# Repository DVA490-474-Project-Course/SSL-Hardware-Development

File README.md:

# SSL-Hardware-Development

## Overview
Welcome to the SSL Robot Project repository! This project encompasses both hardware and software components essential for building and controlling an SSL robot. Our goal is to create a robust, scalable, and maintainable robot platform.

## Repository Structure
- **3D_Models**: Contains all 3D models related to the robot design.
- **Circuits**: Circuit designs for various robot components.
- **BOM**: Bill of Materials for each component.
- **Software**: Firmware and software for motor control and other functionalities.
- **Design_Documents**: Technical specifications and design decisions.
- **Meeting_Notes**: Documentation of project meetings.
- **Misc**: Miscellaneous files and references.
- **Simulations**: Simulation scripts and models.
- **Documentation**: Comprehensive project documentation and guides.

```bash
/SSL-Robot-Project
├── /3D_Models
│   ├── /CAD_Files            # All CAD files for different robot parts
│   ├── /STL_Files            # STL exports for 3D printing
│   └── /Renderings           # Renders of the 3D models
├── /Circuits
│   ├── /Motor_Control        # Motor circuit design files
│   ├── /Kicker               # Kicker circuit design files
│   ├── /Dribbler             # Dribbler circuit design files
│   └── /Sensor               # Sensor circuit design files
├── /BOM                      # Bill of Materials for different components
├── /Software
│   ├── /Motor_Control
│   │   ├── /Firmware          # Firmware code for motor controllers
│   │   │   ├── /src           # Source code files
│   │   │   ├── /include       # Header files
│   │   │   ├── /tests         # Unit and integration tests
│   │   │   └── README.md      # Firmware-specific documentation
│   │   ├── /Software_Doc      # Documentation related to motor control software
│   │   │   ├── /API_Docs      # API documentation if applicable
│   │   │   └── /User_Guides   # User manuals or setup guides
│   │   ├── /Libraries         # Any libraries or dependencies specific to motor control
│   │   └── /Examples          # Example projects or usage scenarios
│   ├── /Kicker_Control        # Similar structure for kicker control software
│   ├── /Dribbler_Control      # Similar structure for dribbler control software
│   └── /Sensor_Control        # Similar structure for sensor control software
├── /Design_Documents          # Technical specifications, design decisions
├── /Meeting_Notes             # Notes from each project meeting
├── /Misc                      # Any other miscellaneous files
├── /Simulations               # Simulation files or scripts if applicable
├── /Documentation             # General documentation for the project
│   ├── README.md              # Overview of the project
│   ├── CONTRIBUTING.md        # Guidelines for contributing
│   ├── LICENSE.md             # Licensing information
│   └── /Wiki_Links            # Links to relevant wiki pages
└── .gitignore                 # Git ignore file
```

## Getting Started

### Prerequisites
- **Hardware**: Access to the necessary hardware components as listed in the BOM.
- **Software**: Install required software dependencies (refer to [Dependencies](Software/Software_Dependencies.md) documentation).

### Setup Instructions
1. **Clone the Repository**
    ```bash
    git clone git@github.com:DVA490-474-Project-Course/SSL-Hardware-Development.git
    cd SSL-Robot-Project
    ```

2. **Setup Software Environment**
    - Navigate to the software directory:
        ```bash
        cd Software/Motor_Control
        ```
    - Follow the instructions in `README.md` to build and deploy the firmware.

3. **Accessing Documentation**
    - Visit the [Wiki](https://github.com/DVA490-474-Project-Course/SSL-Hardware-Development/wiki) for detailed guides and API documentation.

## Contributing
We welcome contributions! Please read our [CONTRIBUTING.md](Documentation/CONTRIBUTING.md) for guidelines on how to get involved.

## License
This project is licensed under the [MIT License](Documentation/LICENSE.md).

## Contact
For any questions or support, please open an issue or contact the project maintainers.

Pontus Svensson - psn19003@student.mdu.se

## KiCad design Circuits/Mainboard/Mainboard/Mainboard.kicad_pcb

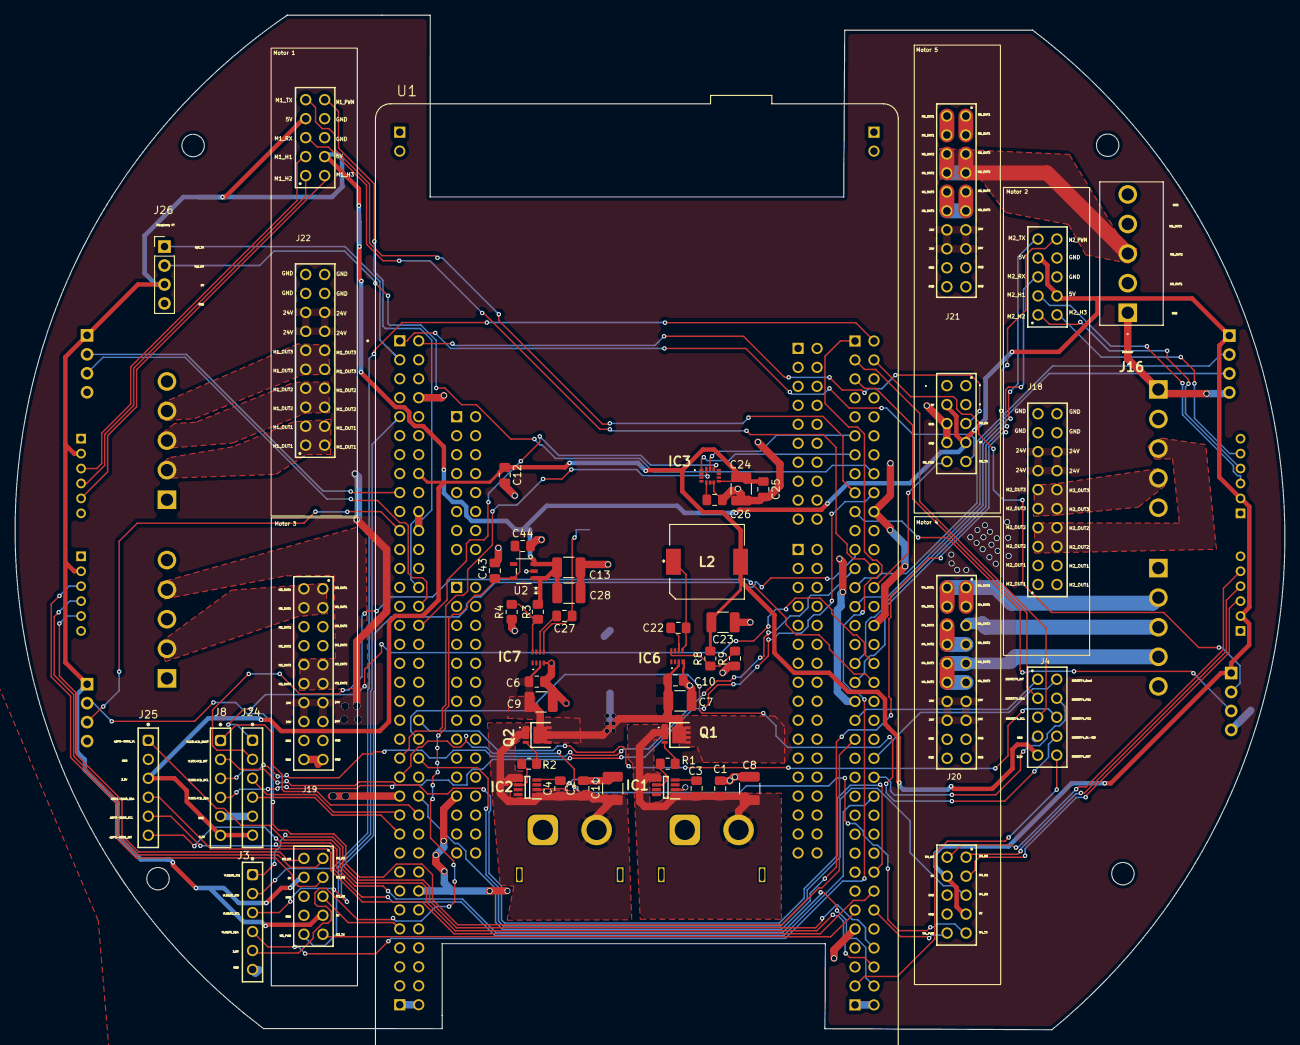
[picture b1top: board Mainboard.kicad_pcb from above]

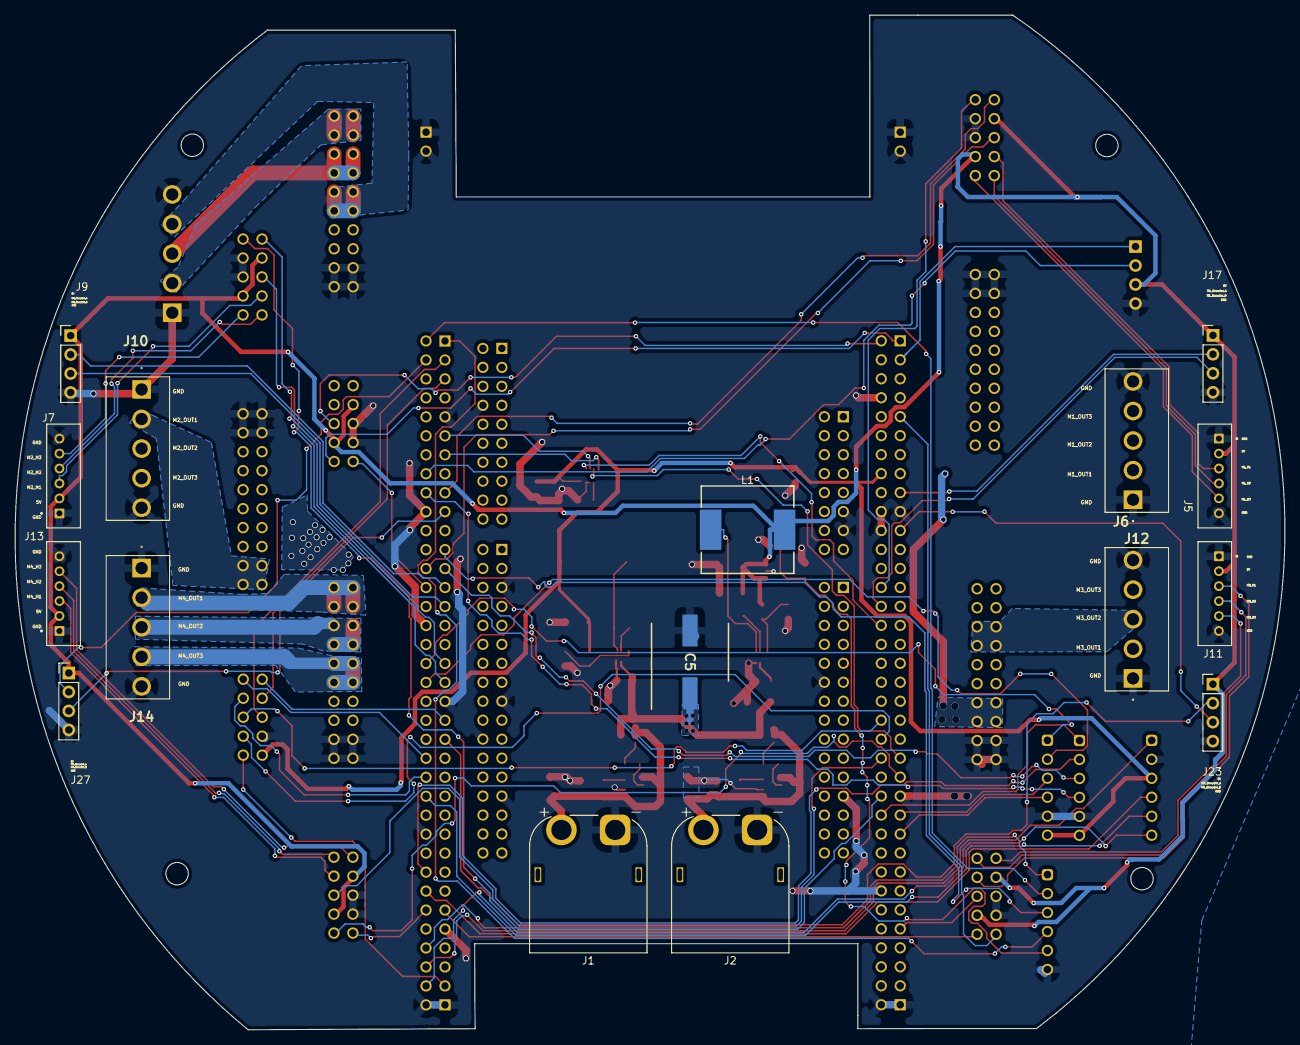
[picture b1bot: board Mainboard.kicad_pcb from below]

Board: 2 copper layers, 170.0 x 135.9 mm, 65 parts (16 on the bottom side), 100 nets.

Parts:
C1, C2, C3, C4, C6, C10, C12, C22, C25, C26, C27, C44: 0.1uF; C_0805_2012Metric_Pad1.18x1.45mm_HandSolder
C5: 220uF; CAPAE1030X1050N
C7, C8, C9, C11, C13, C24: 10uF; C_1210_3225Metric_Pad1.33x2.70mm_HandSolder
C23, C28: 47uF; C_1210_3225Metric_Pad1.33x2.70mm_HandSolder
C43: 4.7uF; C_0805_2012Metric_Pad1.18x1.45mm_HandSolder
IC1, IC2: LM74500QDDFRQ1; SOT65P280X110-8N
IC3: 2536030320001
IC6, IC7: TPS563300DRLR; TPS62932DRLR
J1, J2: XT60PW-M; AMASS_XT60PW-M_1x02_P7.20mm_Horizontal
J3, J8, J24, J25: Conn_01x06_Pin; 61300611821
J4: 61301021821
J5, J7, J11, J13: B6B-PH-K-S; JST_B6B-PH-K-S
J6, J10, J12, J14, J16: B5P-VH_LF__SN_
J9, J17, J23, J26, J27: Conn_01x04_Pin; PinHeader_1x04_P2.54mm_Vertical
J18, J19, J20, J21, J22: ESC_Adapter_socket
L1: 8.2uH; WE-HCC_1210
L2: 5.6uH; 7447714220
Q1, Q2: PSMN6R7-40MLDX; PSMN6R740MLDX
R1, R2: 10; R_0805_2012Metric_Pad1.20x1.40mm_HandSolder
R3: 52.3kOhm; R_0805_2012Metric_Pad1.20x1.40mm_HandSolder
R4, R9: 10kOhm; R_0805_2012Metric_Pad1.20x1.40mm_HandSolder
R8: 30.9kOhm; R_0805_2012Metric_Pad1.20x1.40mm_HandSolder
U1: NUCLEOH723ZG; MODULE_NUCLEOH723ZG
U2: ADP121-AUJZ28R7; UJ-5_ADI

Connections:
2.8V: C43.1, C44.1, J3.5, U2.5 (VOUT)
3.3V: C12.1, C23.2, C24.1, C25.1, IC3.8 (VDD), J4.9, J8.6, J24.6, J25.3, L2.2, R8.2, U1.CN11_16 (3V3)
5V: C13.1, C28.1, J5.2, J7.2, J9.1, J11.2, J13.2, J17.1, J18.24, J18.27, J19.24, J19.27, J20.24, J20.27, J21.24, J21.27, J22.24, J22.27, J23.1, J26.3, J27.1, L1.2, R3.2, U2.1 (VIN), U2.3 (EN)
24V: C5.1, C6.1, C7.1, C9.1, C10.1, IC6.3 (VIN), IC7.3 (VIN), J18.13, J18.14, J18.15, J18.16, J19.13, J19.14, J19.15, J19.16, J20.13, J20.14, J20.15, J20.16, J21.13, J21.14, J21.15, J21.16, J22.13, J22.14, J22.15, J22.16, Q1.5 (D_1), Q1.6 (D_2), Q1.7 (D_3), Q1.8 (D_4), Q1.9 (D_5), Q1.10 (D_6), Q1.11 (D_7), Q2.5 (D_1), Q2.6 (D_2), Q2.7 (D_3), Q2.8 (D_4), Q2.9 (D_5), Q2.10 (D_6), Q2.11 (D_7)
/24V_1: C1.1, C3.1, C8.1, IC1.1 (EN), IC1.5 (SOURCE), J1.2, Q1.1 (S_1), Q1.2 (S_2), Q1.3 (S_3)
/24V_2: C2.1, C4.1, C11.1, IC2.1 (EN), IC2.5 (SOURCE), J2.2, Q2.1 (S_1), Q2.2 (S_2), Q2.3 (S_3)
/ADPS-9960_INT: J25.6, U1.CN12_70 (PG6)
/ADPS-9960_SCL: J25.5, U1.CN12_50 (PF14)
/ADPS-9960_SDA: J25.4, U1.CN12_60 (PF15)
/ADPS-9960_VL: J25.1, U1.CN12_68 (PG5)
/M1_Encoder_A: J17.2, U1.CN11_17 (PA15)
/M1_Encoder_B: J17.3, U1.CN11_30 (PA1)
/M1_H1: J5.3, J22.23
/M1_H2: J5.4, J22.21
/M1_H3: J5.5, J22.22
/M1_OUT1: J6.2, J22.1, J22.2, J22.3, J22.4
/M1_OUT2: J6.3, J22.5, J22.6, J22.7, J22.8
/M1_OUT3: J6.4, J22.9, J22.10, J22.11, J22.12
/M1_PWM: J22.30, U1.CN11_28 (PA0)
/M1_RX: J22.25, U1.CN12_26 (PB15)
/M1_TX: J22.29, U1.CN12_17 (PB6)
/M2_Encoder_A: J9.2, U1.CN12_27 (PB4)
/M2_Encoder_B: J9.3, U1.CN12_29 (PB5)
/M2_H1: J7.3, J18.23
/M2_H2: J7.4, J18.21
/M2_H3: J7.5, J18.22
/M2_OUT1: J10.2, J18.1, J18.2, J18.3, J18.4
/M2_OUT2: J10.3, J18.5, J18.6, J18.7, J18.8
/M2_OUT3: J10.4, J18.9, J18.10, J18.11, J18.12
/M2_PWM: J18.30, U1.CN11_50 (PE5)
/M2_RX: J18.25, U1.CN12_37 (PA3)
/M2_TX: J18.29, U1.CN12_35 (PA2)
/M3_Encoder_A: J23.2, U1.CN12_43 (PD12)
/M3_Encoder_B: J23.3, U1.CN11_21 (PB7)
/M3_H1: J11.3, J19.23
/M3_H2: J11.4, J19.21
/M3_H3: J11.5, J19.22
/M3_OUT1: J12.2, J19.1, J19.2, J19.3, J19.4
/M3_OUT2: J12.3, J19.5, J19.6, J19.7, J19.8
/M3_OUT3: J12.4, J19.9, J19.10, J19.11, J19.12
/M3_PWM: J19.30, U1.CN11_9 (PF6)
/M3_RX: J19.25, U1.CN11_63 (PG9)
/M3_TX: J19.29, U1.CN12_61 (PG14)
/M4_Encoder_A: J27.2, U1.CN12_4 (PC6)
/M4_Encoder_B: J27.3, U1.CN12_19 (PC7)
/M4_H1: J13.3, J20.23
/M4_H2: J13.4, J20.21
/M4_H3: J13.5, J20.22
/M4_OUT1: J14.2, J20.1, J20.2, J20.3, J20.4
/M4_OUT2: J14.3, J20.5, J20.6, J20.7, J20.8
/M4_OUT3: J14.4, J20.9, J20.10, J20.11, J20.12
/M4_PWM: J20.30, U1.CN12_62 (PF11)
/M4_RX: J20.25, U1.CN11_46 (PE2)
/M4_TX: J20.29, U1.CN11_47 (PE3)
/M5_OUT1: J16.2, J21.1, J21.2, J21.3, J21.4
/M5_OUT2: J16.3, J21.5, J21.6, J21.7, J21.8
/M5_OUT3: J16.4, J21.9, J21.10, J21.11, J21.12
/M5_PWM: J21.30, U1.CN12_28 (PB14)
/M5_RX: J21.25, U1.CN11_2 (PC11)
/M5_TX: J21.29, U1.CN11_1 (PC10)
/Rpi_RX: J26.2, U1.CN12_16 (PB12)
/Rpi_TX: J26.1, U1.CN11_3 (PC12)
/SEN0374_BL-IND: J4.8, U1.CN11_44 (PG3)
/SEN0374_Boot: J4.2, U1.CN12_46 (PD14)
/SEN0374_INT: J4.1, U1.CN12_41 (PD13)
/SEN0374_PS1: J4.4, U1.CN12_48 (PD15)
/SEN0374_PS2: J4.6, U1.CN11_42 (PG2)
/SEN0374_RST: J4.10, U1.CN12_69 (PG4)
/SEN0374_SCL: J4.5, U1.CN12_3 (PB8)
/SEN0374_SDA: J4.3, U1.CN12_5 (PB9)
/VL53L4CD2_INT: J24.2, U1.CN12_38 (PF4)
/VL53L4CD2_SCL: J24.3, U1.CN11_51 (PF1)
/VL53L4CD2_SDA: J24.4, U1.CN11_53 (PF0)
/VL53L4CD2_SHUT: J24.1, U1.CN12_36 (PF5)
/VL53L4CD_INT: J8.2, U1.CN12_58 (PF3)
/VL53L4CD_SCL: J8.3, U1.CN12_25 (PB10)
/VL53L4CD_SDA: J8.4, U1.CN12_18 (PB11)
/VL53L4CD_SHUT: J8.1, U1.CN11_52 (PF2)
/VL6180_IO0: J3.2, U1.CN12_2 (PC8)
/VL6180_IO1: J3.1, U1.CN12_66 (PG8)
/VL6180_SCL: J3.3, U1.CN12_23 (PA8)
/VL6180_SDA: J3.4, U1.CN12_1 (PC9)
GND: C1.2, C2.2, C5.2, C6.2, C7.2, C8.2, C9.2, C10.2, C11.2, C12.2, C13.2, C23.1, C24.2, C25.2, C26.2, C28.2, C43.2, C44.2, IC1.2 (GND), IC2.2 (GND), IC3.6 (GND_1), IC3.7 (GND_2), IC6.4 (GND), IC7.4 (GND), J1.1, J2.1, J3.6, J4.7, J5.1, J5.6, J6.1, J6.5, J7.1, J7.6, J8.5, J9.4, J10.1, J10.5, J11.1, J11.6, J12.1, J12.5, J13.1, J13.6, J14.1, J14.5, J16.1, J16.5, J17.4, J18.17, J18.18, J18.19, J18.20, J18.26, J18.28, J19.17, J19.18, J19.19, J19.20, J19.26, J19.28, J20.17, J20.18, J20.19, J20.20, J20.26, J20.28, J21.17, J21.18, J21.19, J21.20, J21.26, J21.28, J22.17, J22.18, J22.19, J22.20, J22.26, J22.28, J23.4, J24.5, J25.2, J26.4, J27.4, R4.1, R9.1, U1.CN3_1 (GND_CN3), U1.CN3_2 (GND_CN3), U1.CN4_1 (GND_CN4), U1.CN4_2 (GND_CN4), U1.CN7_8 (GND_CN7), U1.CN8_11 (GND_CN8), U1.CN8_13 (GND_CN8), U1.CN9_12 (GND_CN9), U1.CN9_23 (GND_CN9), U1.CN10_5 (GND_CN10), U1.CN10_17 (GND_CN10), U1.CN10_22 (GND_CN10), U1.CN10_27 (GND_CN10), U1.CN11_8 (GND_CN11), U1.CN11_19 (GND_CN11), U1.CN11_20 (GND_CN11), U1.CN11_22 (GND_CN11), U1.CN11_49 (GND_CN11), U1.CN11_60 (GND_CN11), U1.CN12_9 (GND_CN12), U1.CN12_20 (GND_CN12), U1.CN12_32 (AGND_CN12), U1.CN12_39 (GND_CN12), U1.CN12_54 (GND_CN12), U1.CN12_63 (GND_CN12), U1.CN15_1 (GND_CN15), U1.CN15_2 (GND_CN15), U1.CN16_1 (GND_CN16), U1.CN16_2 (GND_CN16), U2.2 (GND)
unnamed: IC1.6 (GATE), R1.2
unnamed: C3.2, IC1.4 (VCAP)
unnamed: IC2.6 (GATE), R2.2
unnamed: C4.2, IC2.4 (VCAP)
unnamed: C22.2, IC6.6 (BST)
unnamed: IC6.8 (FB), R8.1, R9.2
unnamed: C22.1, IC6.5 (SW), L2.1
unnamed: C27.2, IC7.6 (BST)
unnamed: IC7.8 (FB), R3.1, R4.2
unnamed: C27.1, IC7.5 (SW), L1.1
unnamed: Q1.4 (G), R1.1
unnamed: Q2.4 (G), R2.1
VDD_IO: C26.1, IC3.5 (VDD_IO)
WSENS_CS: IC3.12 (CS), U1.CN11_32 (PA4)
WSENS_SAO: IC3.1 (SAO), U1.CN12_13 (PA6)
WSENS_SCL: IC3.13 (SCL), U1.CN12_11 (PA5)
WSENS_SDA: IC3.14 (SDA), U1.CN11_45 (PD7)

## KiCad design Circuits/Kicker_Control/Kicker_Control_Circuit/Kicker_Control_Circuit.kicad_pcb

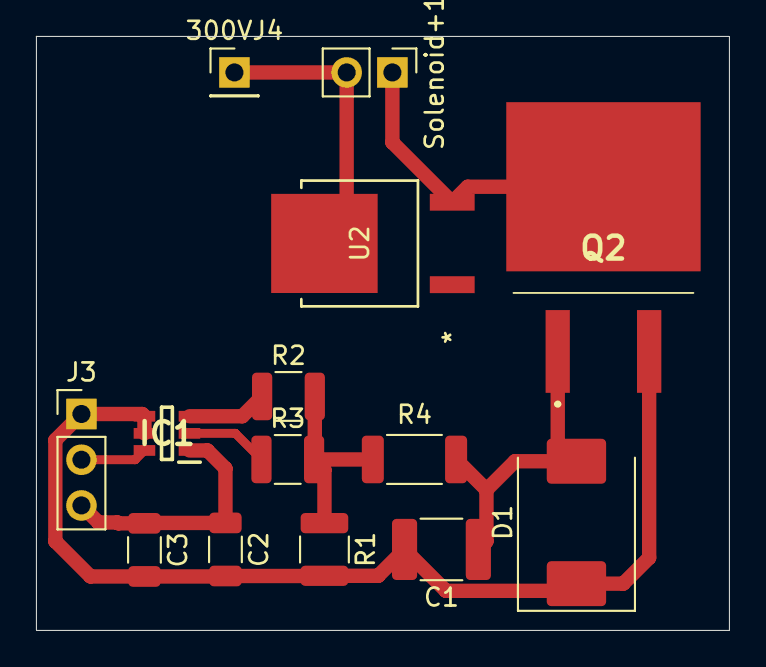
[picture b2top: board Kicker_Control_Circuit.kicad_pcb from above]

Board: 2 copper layers, 38.5 x 33.0 mm, 14 parts (0 on the bottom side), 9 nets.

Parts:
300VJ4: Conn_01x01_Pin; PinHeader_1x01_P2.54mm_Vertical
C1: 0.1u; C_1812_4532Metric
C2: 0.1u; C_1206_3216Metric
C3: 1u; C_1206_3216Metric
D1: Diode; D_SMC
IC1: UCC27511DBVR; SOT95P280X145-6N
J3: Conn_01x03_Pin; PinHeader_1x03_P2.54mm_Vertical
Q2: IKB40N65ES5ATMA1; BTS141TCBUMA1
R1, R2, R3: 10k; R_1210_3225Metric
R4: 100; R_2010_5025Metric
Solenoid+1: Solenoid-; PinHeader_1x02_P2.54mm_Vertical
U2: VS-5EWH06FN-M3; DPAK_06FN-M3_VIS

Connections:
/15V: C2.1, C3.1, IC1.1 (VDD), J3.3
/GND: C1.2, C2.2, C3.2, D1.1 (A), IC1.4 (GND), IC1.5 (IN-), J3.1, Q2.3 (E), R1.2
/On_Signal 3V: IC1.6 (IN+), J3.2
/Output1_Solenoid: 300VJ4.1, Solenoid+1.2, U2.2
/Output2_Solenoid: Q2.2 (C), Solenoid+1.1, U2.3
unnamed: C1.1, D1.2 (C), Q2.1 (G), R4.2
unnamed: IC1.2 (OUTH), R3.1
unnamed: IC1.3 (OUTL), R2.1
unnamed: R1.1, R2.2, R3.2, R4.1

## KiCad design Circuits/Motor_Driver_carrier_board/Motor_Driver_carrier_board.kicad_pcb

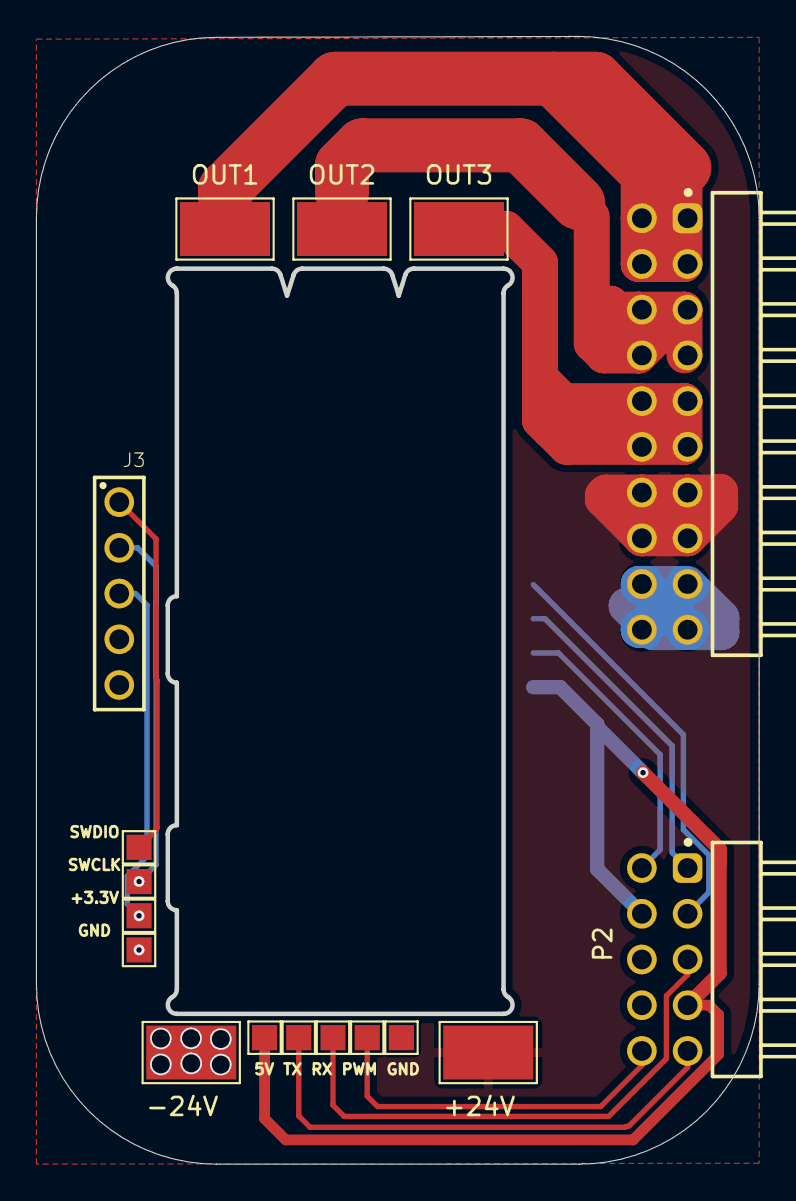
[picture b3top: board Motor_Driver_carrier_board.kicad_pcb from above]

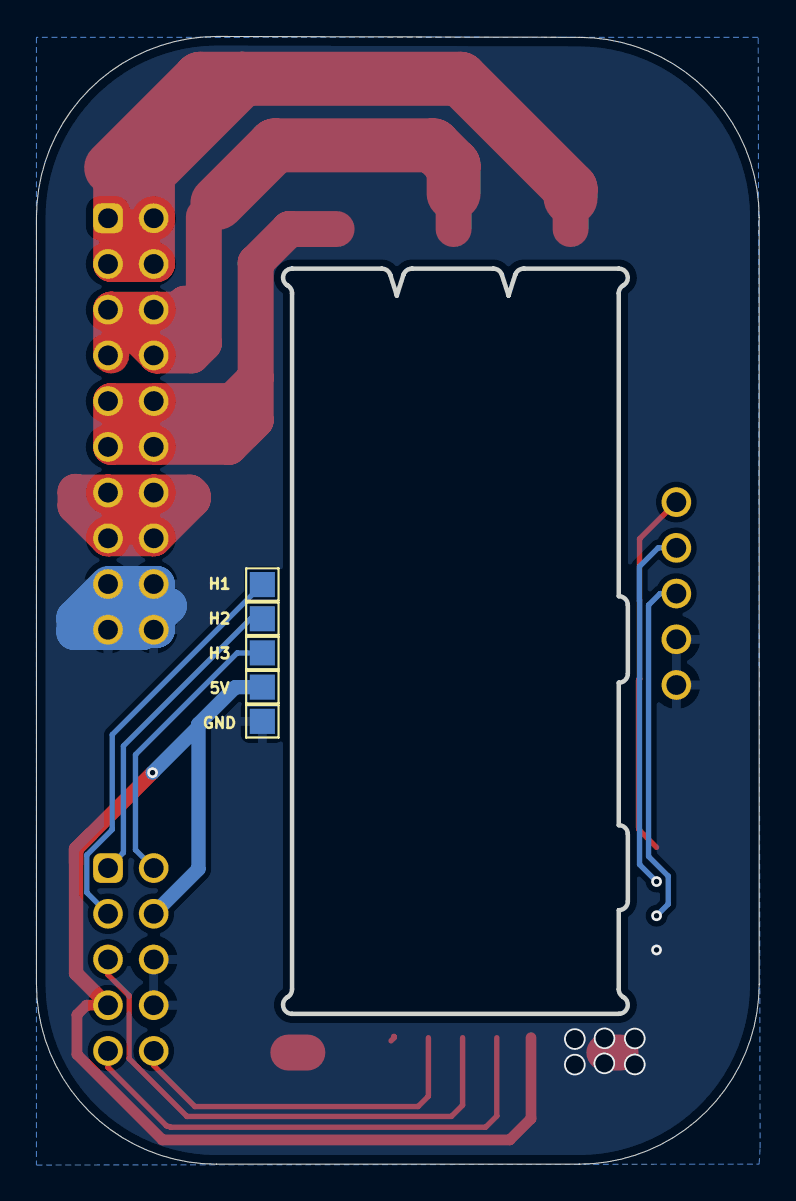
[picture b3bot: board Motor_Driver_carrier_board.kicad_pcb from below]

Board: 2 copper layers, 40.2 x 62.7 mm, 21 parts (5 on the bottom side), 15 nets.

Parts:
5V, 5V#2: TestPoint_Pad_1.4x1.4mm; TestPoint_Pad_1.0x1.0mm
+3.3V: TestPoint_Pad_1.4x1.4mm; TestPoint_Pad_1.0x1.0mm
+24V: OUT1; Solder_Pad_5.0x3.0mm
-24V: OUT1; Solder_Pad_5.0x3.0mm
GND: TestPoint_Pad_1.4x1.4mm; TestPoint_Pad_1.0x1.0mm
GND#2, GND#3: TestPoint_Pad_1.4x1.4mm; TestPoint_Pad_1.0x1.0mm
H1, H2, H3: TestPoint_Pad_1.4x1.4mm; TestPoint_Pad_1.0x1.0mm
J3: 61300511121
OUT1, OUT2, OUT3: OUT1; Solder_Pad_5.0x3.0mm
P2: ESC_Adapter_pins_right_angle
PWM: TestPoint_Pad_1.4x1.4mm; TestPoint_Pad_1.0x1.0mm
RX: TestPoint_Pad_1.4x1.4mm; TestPoint_Pad_1.0x1.0mm
SWCLK: TestPoint_Pad_1.4x1.4mm; TestPoint_Pad_1.0x1.0mm
SWDIO: TestPoint_Pad_1.4x1.4mm; TestPoint_Pad_1.0x1.0mm
TX: TestPoint_Pad_1.4x1.4mm; TestPoint_Pad_1.0x1.0mm

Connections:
3.3V: +3.3V.1, J3.3
5V: 5V.1, 5V#2.1, P2.24, P2.27
24V: +24V.1, P2.13, P2.14, P2.15, P2.16
GND: -24V.1, GND#2.1, GND#3.1, J3.4, J3.5, P2.17, P2.18, P2.19, P2.20, P2.26, P2.28
H1: H1.1, P2.23
H2: H2.1, P2.21
H3: H3.1, P2.22
OUT1: OUT1.1, P2.1, P2.2, P2.3, P2.4
OUT2: OUT2.1, P2.5, P2.6, P2.7, P2.8
OUT3: OUT3.1, P2.9, P2.10, P2.11, P2.12
PWM: P2.30, PWM.1
RX: P2.25, RX.1
SWCLK: J3.2, SWCLK.1
SWDIO: J3.1, SWDIO.1
TX: P2.29, TX.1

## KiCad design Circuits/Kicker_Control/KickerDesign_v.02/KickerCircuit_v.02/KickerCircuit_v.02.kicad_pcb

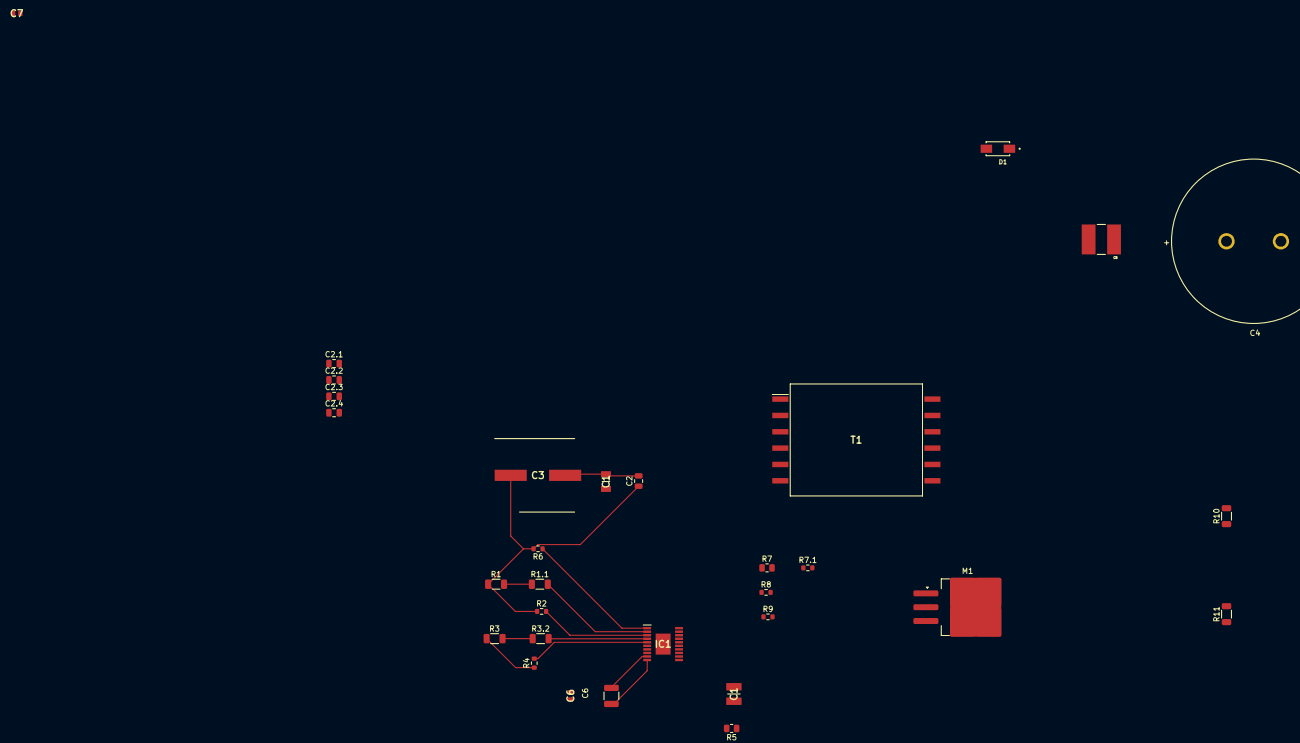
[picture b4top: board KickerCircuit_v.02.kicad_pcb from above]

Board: 2 copper layers, 31 parts (0 on the bottom side), 21 nets.

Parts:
C1: 885012208069; CAPC3216X180N
C1#2: 10uF (885012209073); CAPC3225X280N
C2, C2.1: 2.2uF; C_0805_2012Metric
C2.2, C2.3, C2.4: 2.2u; C_0805_2012Metric
C3: 680 uF (865080562017); CAPAE1350X1400N
C4: WCAP-AIG8_30X46; WCAP-AIG8_30X46_DXL_
C5: CKG57NX7R2J474M500JH; CAPC6050X550N
C6: 10uF; C_1210_3225Metric
C6#2: 10000 pF (885342206006); CAPC1608X87N
C7: 885342206006 (10000 pF); CAPC1608X87N
D1: US1M; DIOM4325X250N
IC1: LT3751IFE#PBF; SOP65P640X120-21N
M1: NMOS; TO-263-3_TabPin2
R1, R3: 1.8k; R_1206_3216Metric
R1.1, R3.2: 68k; R_1206_3216Metric
R2, R4: 475k; R_0603_1608Metric
R5: 6m; R_0805_2012Metric
R6, R8: 40.2k; R_0603_1608Metric
R7: 200; R_0805_2012Metric
R7.1: 18k; R_0603_1608Metric
R9: 4.02k; R_0603_1608Metric
R10: 30.9k; R_1206_3216Metric
R11: 383; R_1206_3216Metric
T1: DA2034-ALD; SOP300P3000X1143-12N

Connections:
GND: C1.1, C1#2.1, C2.2, C2.1.2, C2.2.2, C2.3.2, C2.4.2, C3.2 (-), C4.2, C5.2, C6.2, C6#2.2, C7.2, IC1.9 (CLAMP), IC1.11 (CSN), R5.1, R9.2, R11.2, T1.12 (SEC_2)
unnamed: IC1.12 (CSP), M1.3 (S), R5.2
unnamed: C6.1, C6#2.1, C7.1, IC1.10 (FB), R10.2, R11.1
unnamed: IC1.15 (HVGATE), M1.2 (G)
unnamed: IC1.3 (OVLO1), R2.2
unnamed: IC1.5 (OVLO2), R4.2
unnamed: IC1.16 (RBG), R9.1
unnamed: IC1.20 (RDCM), R7.1
unnamed: IC1.18 (RVOUT), R8.1
unnamed: IC1.1 (RVTRANS), R6.1
unnamed: IC1.2 (UVLO1), R1.1.2
unnamed: IC1.4 (UVLO2), R3.2.2
unnamed: C1.2, C1#2.2, IC1.13 (VCC)
unnamed: M1.1 (D), R7.1.2, R8.2, T1.7 (PRI_5), T1.8 (PRI_6), T1.9 (PRI_7), T1.10 (PRI_8)
unnamed: R1.2, R1.1.1
unnamed: R3.2, R3.2.1
unnamed: R7.2, R7.1.1
unnamed: D1.A, T1.1 (SEC_1)
Vcc: IC1.14 (LVGATE), R3.1, R4.1
Vout: C4.1, C5.1, D1.C, R10.1
Vtrans: C2.1, C2.1.1, C2.2.1, C2.3.1, C2.4.1, C3.1 (+), R1.1, R2.1, R6.2, T1.3 (PRI_1), T1.4 (PRI_2), T1.5 (PRI_3), T1.6 (PRI_4)

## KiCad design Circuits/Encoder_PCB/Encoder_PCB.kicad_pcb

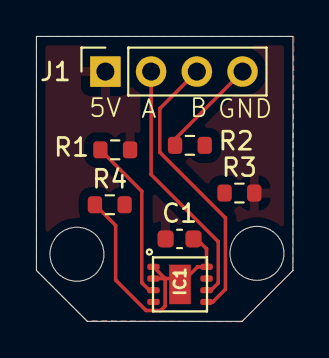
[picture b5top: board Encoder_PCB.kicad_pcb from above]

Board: 2 copper layers, 14.3 x 15.8 mm, 7 parts (0 on the bottom side), 6 nets.

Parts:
C1: 100n; C_0603_1608Metric
IC1: iC-PX2604; ODFN8-3X3
J1: Conn_01x04_Socket; PinSocket_1x04_P2.54mm_Vertical
R1: 0R; R_0603_1608Metric
R2, R3, R4: N/A; R_0603_1608Metric

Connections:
+5V: C1.1, IC1.7 (VDD), J1.1, R1.2, R3.2
/CH-A: IC1.6 (A), J1.2
/CH-B: IC1.5 (B), J1.3
GND: C1.2, IC1.1 (TM1), IC1.2 (TM2), IC1.8 (GND), IC1.BP (GND), J1.4, R2.1, R4.1
unnamed: IC1.3 (SEL1), R1.1, R2.2
unnamed: IC1.4 (SEL2), R3.1, R4.2

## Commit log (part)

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2024-09-23 removed fp-info-cache file from battery folder
2024-09-23 Added two break beam sensors, one with a 5mm beam and one with a 3mm beam. A 5mm beam is a bit more robust and that might be important since there most likely will be some collision with other robots.
2024-09-23 Updated the BOM lists with additional components.
2024-09-24 Created an initial kicker circuit
2024-09-24 Changed communication column since the ESP32 supports Wifi there is no need for additional communication hardware.
2024-09-24 Added component LT3750 which I created in KiCAD
2024-09-24 Added a few comments and addtional hardware to the BOM. After speaking with Emil it was suggested that it would be beneficial to make sure that the camera and the microcontroller support each other.
2024-09-24 Finished the BOM for communication and sensors. Added the last obsticle detection sensor, an ESP32-CAM which includes a camera as well as a development board.
2024-09-24 Created an initial circuit for the dribbler
2024-09-24 Changed the Kicker subcircuit link
2024-09-24 gitignore kicad lck files
2024-09-25 Added sections and another motor driver
2024-09-25 added connector for control signal
2024-09-25 Updated the BOM.xlsx with the components/sensors from RoboCUP_SSL_Hardware_BOM.xlsx
2024-09-25 Added a few comments and additional retailers based on the feedback we reveived from Henrik Falk.
2024-09-25 Updated the Capacitor Charger Circuit
2024-09-25 Added input to the Kicker circuit
2024-09-25 Project ideas
2024-09-25 Updated solenoid controller
2024-09-26 Added comment in the kicker circuit
2024-09-26 Added a discharge circuit for saftey reasons to the capacitor charger
2024-09-26 Updated a few of the links to the retailer website. One based on the feedback given by Henrik on preferred retailers and another since the previous was not up to date. I also added a sheet with the v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
2024-09-26 Added a circuit and made some small changes in the kicker circuit
2024-09-27 Removed the files pertaining to youtube tutorial.
2024-09-27 Created folders for the buck converters that will be created. We need to have buck converters from 24V to 3.3, 5, 12, and 15V.
2024-09-27 Changed the organisation of the excel files. Instead of having the voltage of the sensors as a sheet in BOM.xlsx I created a new excel file with the same information and put the file in Circuits/Volt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
2024-09-27 Made changes in the circuit
2024-09-30 Stakeholder meeting notes
2024-09-30 File with design requirements for the ssl camera system
2024-09-30 Removed tracking of files starting with #
2024-09-30 Formatting
2024-09-30 Just changed the name of the sheet.
2024-09-30 Updated kicker circuit
2024-09-30 Added voltage dividers to the BOM.
2024-10-01 Updated the obsticle detection sensor section with up to date links and prices. Also promoted that the Raspberry Pi 4 Model B/8GB is the one we would like so that we can run both object detection as 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
2024-10-01 Changed the colour classification of the obsticle sensors.
2024-10-01 added a simple dribbler circuit diagram
2024-10-01 Added another bldc motor
2024-10-02 Cleanded and sorted the file.
2024-10-02 Made some minor changes to the BOM
2024-10-02 added ball bearings CAD file for the dribbler
2024-10-03 Added components to the BOM
2024-10-03 Some changes in the circuit
2024-10-03 Added components
2024-10-04 Added the break beam sensor that has been lost. I also included comments to the prices that I know include moms.
2024-10-04 Updated the BOM kicker
2024-10-06 Tips form lennie
2024-10-06 motor circuit kicad, STSPIN32F0 with SQS mosfets
2024-10-07 updated the kicker bom
2024-10-08 updated the BOM for the kicker.
2024-10-09 Added components to the BOM and updated the capacitor circuit
2024-10-09 Added components to the kicker BOM
2024-10-10 Updated the BOM capacitor
2024-10-10 Alternative motor driver circuit
2024-10-10 Added bearings and changed the gate driver to stspin32f0a
2024-10-10 Added alternative motor driver B-G431B-ESC1, Nucleo 144 Dev board as alternative to ESP32, RF tranceivers that are proven to be reliable for communication with server laptop
2024-10-10 Updated ranking color of B-G431B-ESC1
2024-10-10 Changed ranking of the wheel encoders and calculated sum for 1 robot
2024-10-11 demo commit
2024-10-11 Updated the BOM and created a folder for encoder IC for the AEDB-9140-A13.
2024-10-11 Added passive components in the BOM for the kicker
2024-10-11 Added a folder called 'Encoder circuits' with an IC schematic for how the optical encoder AEDB-9140-A13 should be connected according to its datasheet.
2024-10-11 Hardware design reasons for component choice
2024-10-11 Added a directory called 'IMU Circuit' in 'Circuits' directory. Also started the IC for the IMU.
2024-10-12 Added latex documents to gitignore, git rm -r --cached . to update the branch
2024-10-12 Updated architecture/main.tex for hardware design presentation, accidently added *.pdf to the .gitignore, tried to revert any missing pdfs
2024-10-12 Added kicker components to the excel BOM file, exported all components to a csv file to streamline adding components and avoiding merge conflicts. Please use the CSV file to add your components
2024-10-12 Added some of the kicker components to BOM.xlsx
2024-10-12 Renamed BOM_Copy.csv to BOM.csv
2024-10-13 Added sources for the hardware design proposition, motor part, dribbler, motor driver
2024-10-13 Added bbl, blg to gitignore Latex
2024-10-13 microcontroller, raspberry pi justification for our hardware
2024-10-14 added fasteners to BOM
2024-10-14 added dribbler circuit png file
2024-10-14 Filled out all sections for our components in main.tex
2024-10-14 BOM.csv: Removed components we dont want to buy
2024-10-14 BOM.csv: Removed whitespaces
2024-10-14 BOM.csv: Added 'In stock' to B-G ESC1
2024-10-14 Main.tex: Added alternative way to calculate RPM of the wheels
2024-10-14 added threaded inserts to BOM
2024-10-14 Main.tex: Added hardware_architecture image, timeframe limitation for the dribbler and raspberry pi, BOM.xlsx: Changed the ranking of the ESC components
2024-10-14 BOM.xlsx: Changed the ranking of the ESC components
2024-10-14 BOM.csv: Added reverse polarity protection component
2024-10-14 Main.tex: Fixed grammar and typos
2024-10-14 BOM.csv: Added mosfet for the polarity protection circuit
2024-10-14 Finished the IC for the IMU.
2024-10-14 BOM_wurth.csv: Added more bypass capacitors
2024-10-14 BOM.csv: Added components for reverse voltage protection circuit
2024-10-14 Main.tex: Added TVS diodes to the BOM
2024-10-14 BOM.csv: Removed unused component, ESC controller
2024-10-14 added wheel related tems to the BOM.
2024-10-14 Main.tex: Added information about 5010 drone motors
2024-10-14 BOM_wurth.csv: Added pin headers for the nucleo board
2024-10-15 Changed the O-ring size in the bom
2024-10-15 Main.tex: Added alternative table where we will include parts similar to UdeA
2024-10-15 BOM.xlsx: Added UdeA components that we can buy
2024-10-15 Created a new directory in which I will collect the files with code to test the sensors.
2024-10-15 changed to a flanged bearing and X-ring instead.
2024-10-15 Main.tex: Added alternative BOM and replacement components
2024-10-15 BOM.xlsx: Added RGB color sensor that UdeA uses
2024-10-15 Main.tex: Added consideration for UdeA about components, extended the BOMs with more components
2024-10-15 BOM.csv: calculated price
2024-10-15 Main.tex: Typos and made the text coherent
2024-10-15 Main.pdf: Recompiled
2024-10-15 Main.tex: Fixed no borders around table of content
2024-10-15 Main.tex: Removed bookmark plugin to use hyprref instead
2024-10-16 Created BOMS for printing
2024-10-17 BOM.xlsx: Added UdeA components
2024-10-17 Made a copy of main.pdf, stakeholder meeting notes
2024-10-17 BOM.csv: Added all components that was approved to order, added a 9Dof BNO055 IMU
2024-10-17 added pillow blocks for the wheels, updated bearings and amount of bearings.
2024-10-17 BOM.csv: Merged, ordered components by seller, updated prices on components from elefun
2024-10-17 BOM.xlsx: Added connectors section
2024-10-17 changed flange bearing total cost and the total sum to match.
2024-10-17 Created pdf for the bom we are to order and moved udebom
2024-10-17 Started kicad project for the mainboard which will host all components
2024-10-17 BOM.csv: Added components for the kicker circuit
2024-10-17 BOM.csv: Removed THT transistor
2024-10-17 Added footprints and schematic symbols for XT60 connector and LM74599
2024-10-17 Mainboard: Placed connectors and reverse protection components
2024-10-17 removed flanged bearings while awaiting cost proposal and fixed pillow block link
2024-10-17 added .gitattributes to .gitignore
2024-10-17 BOM.csv: Merged with HEAD
2024-10-17 removed extra washers row from BOM
2024-10-17 Fixed pillow block link again
2024-10-17 Merged with new mosfets
2024-10-17 Added all ORing components and reverse voltage protection components
2024-10-17 BOM_wurth.csv: Added component value
2024-10-17 Added components that we will use on the mainboard to kicad
2024-10-17 BOM_wurth.csv: Added Socket headers and pin headers and resistors and added footprint in the description
2024-10-17 BOM_wurth.csv: Added more headers
2024-10-17 Added headers in the circuit for the mainboard in kicad
2024-10-18 Removed unused components and added the rest of the nucleo to kicad schematic
2024-10-18 Added 3D models for the pcb components
2024-10-18 Added datasheets to all our components
2024-10-18 Good information
2024-10-25 Added components for mainboard
2024-10-25 Added socket headers and capacitors for mainboard
2024-10-25 Updated price
2024-10-25 Removed unused
2024-10-27 Added pin headers
2024-10-27 Completet motor driver adapter board, added components for 3d rendering
2024-10-27 Removed wrong datasheet for motor driver
2024-10-27 Added git lfs for tracking large files
2024-10-27 Reverted gitignore changes
2024-10-27 Do not track mainboard.step since it is too large
2024-10-27 Removed cached mainboard.step since it is too large
2024-10-27 Zipped mainboard .step to decrease the size
2024-10-27 Abosulte path of file to ignore
2024-10-27 Removed cached files that was tracked but should not be tracked
2024-10-27 Forced track zip file
2024-10-27 Removed tracking of specific file
2024-10-27 Step file for the mainboard pcb
2024-10-28 Step file for mainboard pcb updated layout
2024-10-29 Version 2 of kicker.
2024-11-06 Removed unused files and updated .DS_Store files
2024-11-06 Document for udeA, mainboard 3d model update, wsen datasheet
2024-11-06 STP to pointer
2024-11-06 Pin configuration in pdf
2024-11-06 Specs for motor, wsen-isds datasheet
2024-11-06 Added updated pin configuration to stm32
2024-11-06 Updated our BOM explanation document
2024-11-06 Updated pin connections for the mainboard controller
2024-11-07 Updated the kicker circuit
2024-11-07 Added stm32cubemx project
2024-11-08 Routing tracks
2024-11-08 Mainborad routing
2024-11-10 Changes in the circuit
2024-11-11 Encoder PCB done, with step file
2024-11-11 Mainboard step file updated
2024-11-12 Changes in the kicker circuit
2024-11-12 Exported mainboard, carrier board, and encoder to gerber
2024-11-13 kicker circuit changest
2024-11-13 Updated the capacitor footprints to 0805, since everyone was different. Added powerplane and groundplane, vias for ground connections, added a connector to for the solenoid to a 1x2 pin headers since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
2024-11-13 Kicker_control cache
2024-11-14 Removed lfs tracking of step files since it costs money
2024-11-16 Capacitor Charger Circuit 100V
2024-11-18 Removed big files using bfg
2024-11-18 Removed big files
2024-11-18 Exported gerber files
2024-11-20 New 100V capacitor charger circuit
2024-12-13 Deleted unnecessary files
2024-12-13 Allow step files
2024-12-13 Added 3 models to the pcbs
2024-12-13 added step files of CAD parts and assemblies
2024-12-13 Create LICENSE
2024-12-17 Added middle_plate and Base_plate step files
2024-12-17 Added TPE bearing step file
2025-01-03 Added offset step file
2025-01-03 Rename encoder_disk.step to Encoder_disk.step
